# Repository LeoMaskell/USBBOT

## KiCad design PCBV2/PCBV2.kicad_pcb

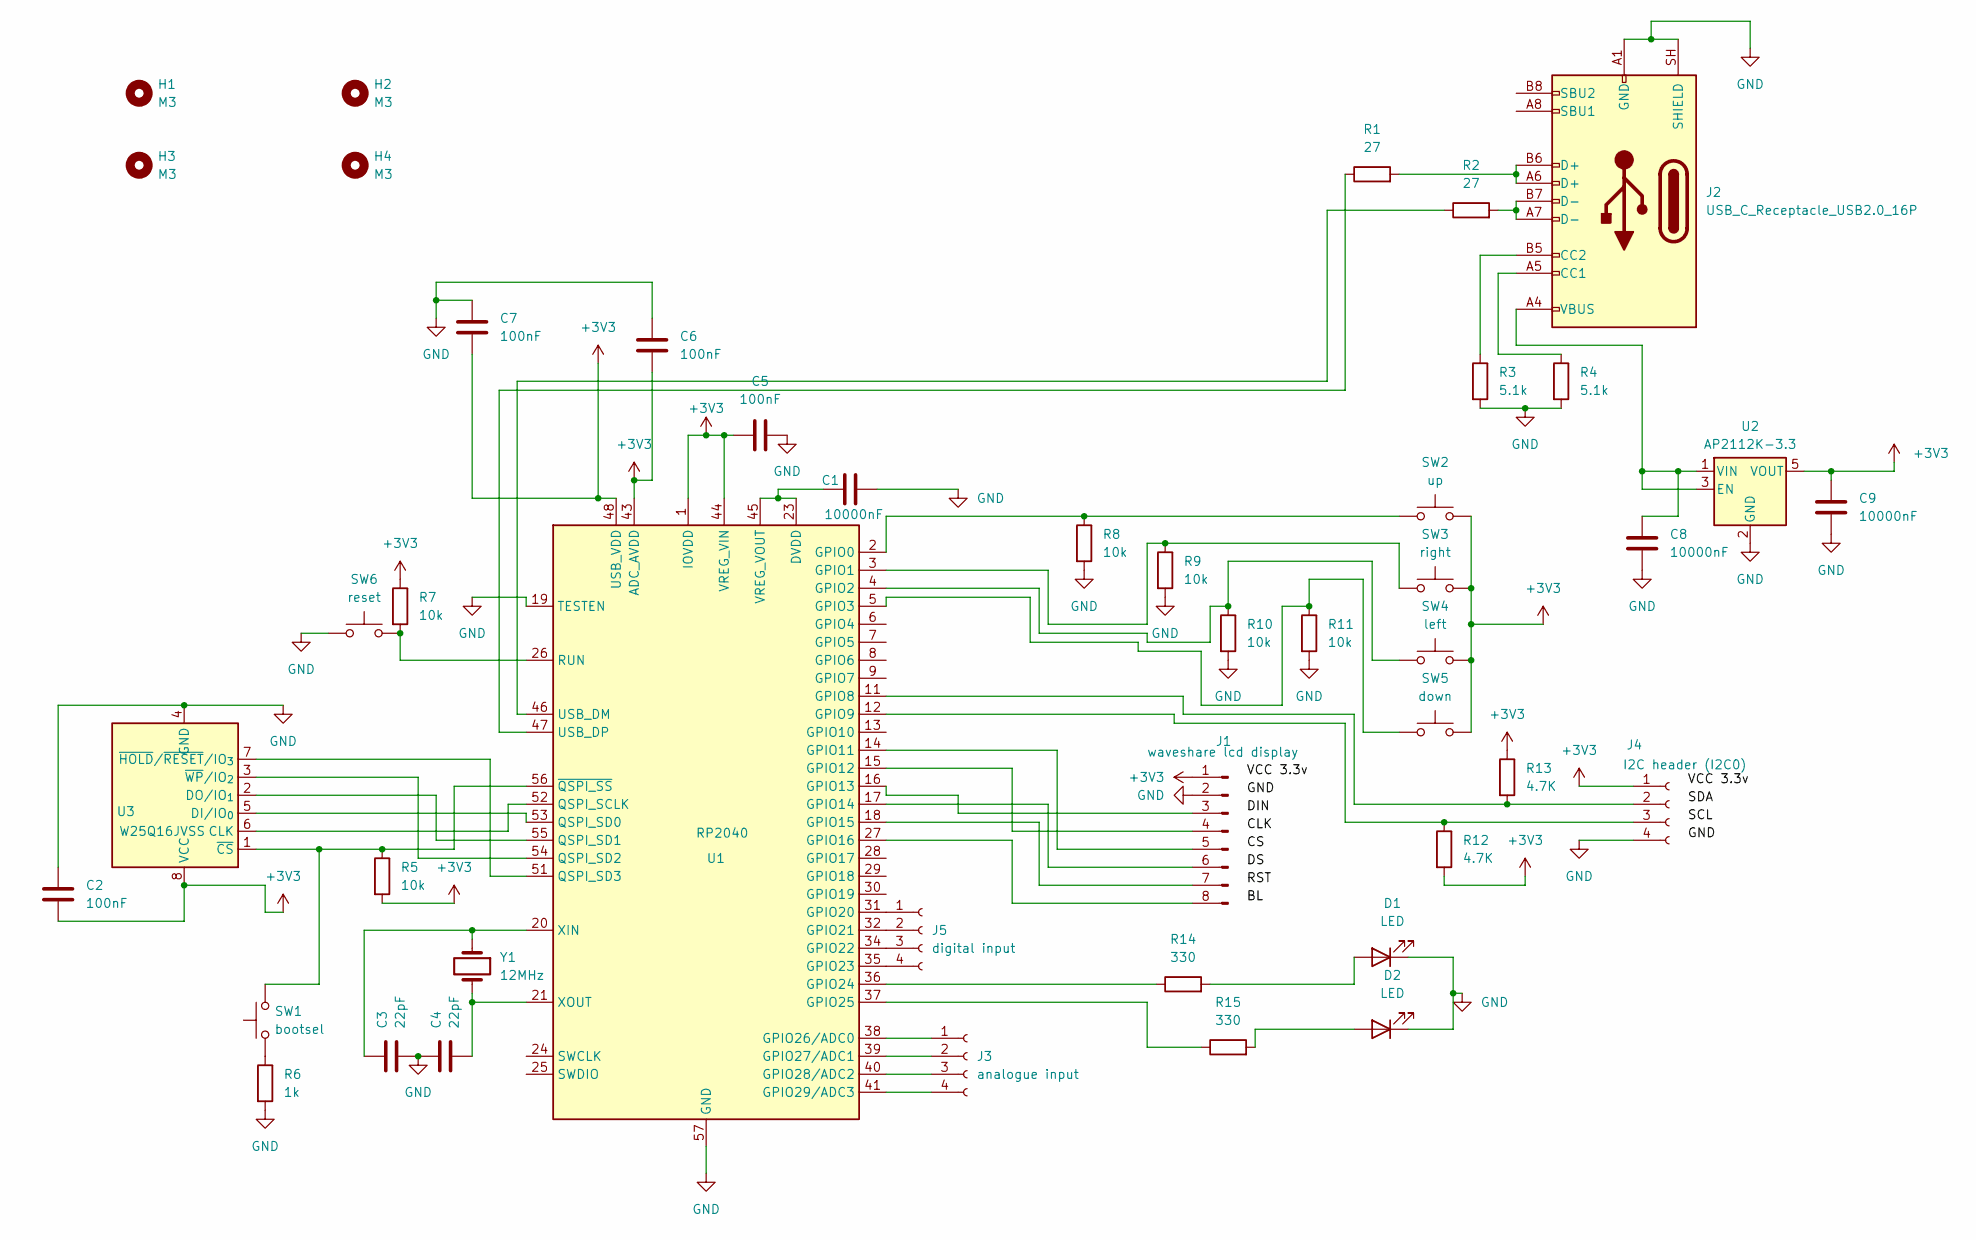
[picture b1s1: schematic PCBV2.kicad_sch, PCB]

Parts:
C1, C8, C9: 10000nF; C_0805_2012Metric
C2, C5, C6, C7: 100nF; C_0603_1608Metric
C3, C4: 22pF; C_0805_2012Metric
D1, D2: LED; LED_D4.0mm
H1, H2, H3, H4: M3; MountingHole_3.2mm_M3
J1: waveshare lcd display; PinHeader_1x08_P2.54mm_Vertical
J2: USB_C_Receptacle_USB2.0_16P; USB_C_Receptacle_Palconn_UTC16-G
J3: analogue input; PinHeader_1x04_P2.00mm_Vertical
J4: I2C header (I2C0); PinHeader_1x04_P2.00mm_Vertical
J5: digital input; PinHeader_1x04_P2.00mm_Vertical
R1, R2: 27; R_0603_1608Metric
R3, R4: 5.1k; R_0603_1608Metric
R5, R7, R8, R9, R10, R11: 10k; R_0603_1608Metric
R6: 1k; R_0603_1608Metric
R12, R13: 4.7K; R_0603_1608Metric
R14, R15: 330; R_0603_1608Metric
SW1: bootsel; SW_SPST_Omron_B3FS-100xP
SW2: up; SW_SPST_Omron_B3FS-100xP
SW3: right; SW_SPST_Omron_B3FS-100xP
SW4: left; SW_SPST_Omron_B3FS-100xP
SW5: down; SW_SPST_Omron_B3FS-100xP
SW6: reset; SW_SPST_Omron_B3FS-100xP
U1: RP2040; QFN-56-1EP_7x7mm_P0.4mm_EP3.2x3.2mm
U2: AP2112K-3.3; SOT-23-5_HandSoldering
U3: W25Q16JVSS; SOIC-8_5.3x5.3mm_P1.27mm
Y1: 12MHz; Crystal_HC49-4H_Vertical

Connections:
+3V3: C2.2, C5.1, C6.2, C7.2, C9.1, J1.1, J4.1, R5.2, R7.1, R12.2, R13.1, SW2.2, SW3.2, SW4.2, SW5.2, U1.1 (IOVDD), U1.10 (IOVDD), U1.22 (IOVDD), U1.33 (IOVDD), U1.42 (IOVDD), U1.43 (ADC_AVDD), U1.44 (VREG_VIN), U1.48 (USB_VDD), U1.49 (IOVDD), U2.5 (VOUT), U3.8 (VCC)
GND: C1.2, C2.1, C3.2, C4.1, C5.2, C6.1, C7.1, C8.2, C9.2, D1.1 (K), D2.1 (K), J1.2, J2.A1 (GND), J2.A12 (GND), J2.B1 (GND), J2.B12 (GND), J2.SH (SHIELD), J4.4, R3.2, R4.2, R6.2, R8.2, R9.2, R10.2, R11.2, SW6.1, U1.19 (TESTEN), U1.57 (GND), U2.2 (GND), U3.4 (GND)
unnamed: D1.2 (A), R14.2
unnamed: D2.2 (A), R15.2
unnamed: J1.3, U1.16 (GPIO13)
unnamed: J1.4, U1.15 (GPIO12)
unnamed: J1.5, U1.14 (GPIO11)
unnamed: J1.6, U1.17 (GPIO14)
unnamed: J1.7, U1.18 (GPIO15)
unnamed: J1.8, U1.27 (GPIO16)
unnamed: J2.A5 (CC1), R4.1
unnamed: J2.B5 (CC2), R3.1
unnamed: J2.A6 (D+), J2.B6 (D+), R1.2
unnamed: J2.A7 (D-), J2.B7 (D-), R2.2
unnamed: J3.1, U1.38 (GPIO26/ADC0)
unnamed: J3.2, U1.39 (GPIO27/ADC1)
unnamed: J3.3, U1.40 (GPIO28/ADC2)
unnamed: J3.4, U1.41 (GPIO29/ADC3)
unnamed: J4.2, R13.2, U1.11 (GPIO8)
unnamed: J4.3, R12.1, U1.12 (GPIO9)
unnamed: J5.1, U1.31 (GPIO20)
unnamed: J5.2, U1.32 (GPIO21)
unnamed: J5.3, U1.34 (GPIO22)
unnamed: J5.4, U1.35 (GPIO23)
unnamed: R6.1, SW1.1
unnamed: R8.1, SW2.1, U1.2 (GPIO0)
unnamed: R9.1, SW3.1, U1.3 (GPIO1)
unnamed: R10.1, SW4.1, U1.4 (GPIO2)
unnamed: R11.1, SW5.1, U1.5 (GPIO3)
unnamed: R14.1, U1.36 (GPIO24)
unnamed: R15.1, U1.37 (GPIO25)
unnamed: U1.52 (QSPI_SCLK), U3.6 (CLK)
unnamed: U1.53 (QSPI_SD0), U3.5 (DI/IO_{0})
unnamed: U1.55 (QSPI_SD1), U3.2 (DO/IO_{1})
unnamed: U1.54 (QSPI_SD2), U3.3 (~WP/IO_{2})
unnamed: U1.51 (QSPI_SD3), U3.7 (~HOLD/~RESET/IO_{3})
unnamed: R7.2, SW6.2, U1.26 (RUN)
unnamed: R2.1, U1.46 (USB_DM)
unnamed: R1.1, U1.47 (USB_DP)
unnamed: C1.1, U1.23 (DVDD), U1.45 (VREG_VOUT), U1.50 (DVDD)
unnamed: C3.1, U1.20 (XIN), Y1.1
unnamed: C4.2, U1.21 (XOUT), Y1.2
unnamed: R5.1, SW1.2, U1.56 (~QSPI_SS), U3.1 (~CS)
unnamed: C8.1, J2.A4 (VBUS), J2.A9 (VBUS), J2.B4 (VBUS), J2.B9 (VBUS), U2.1 (VIN), U2.3 (EN)

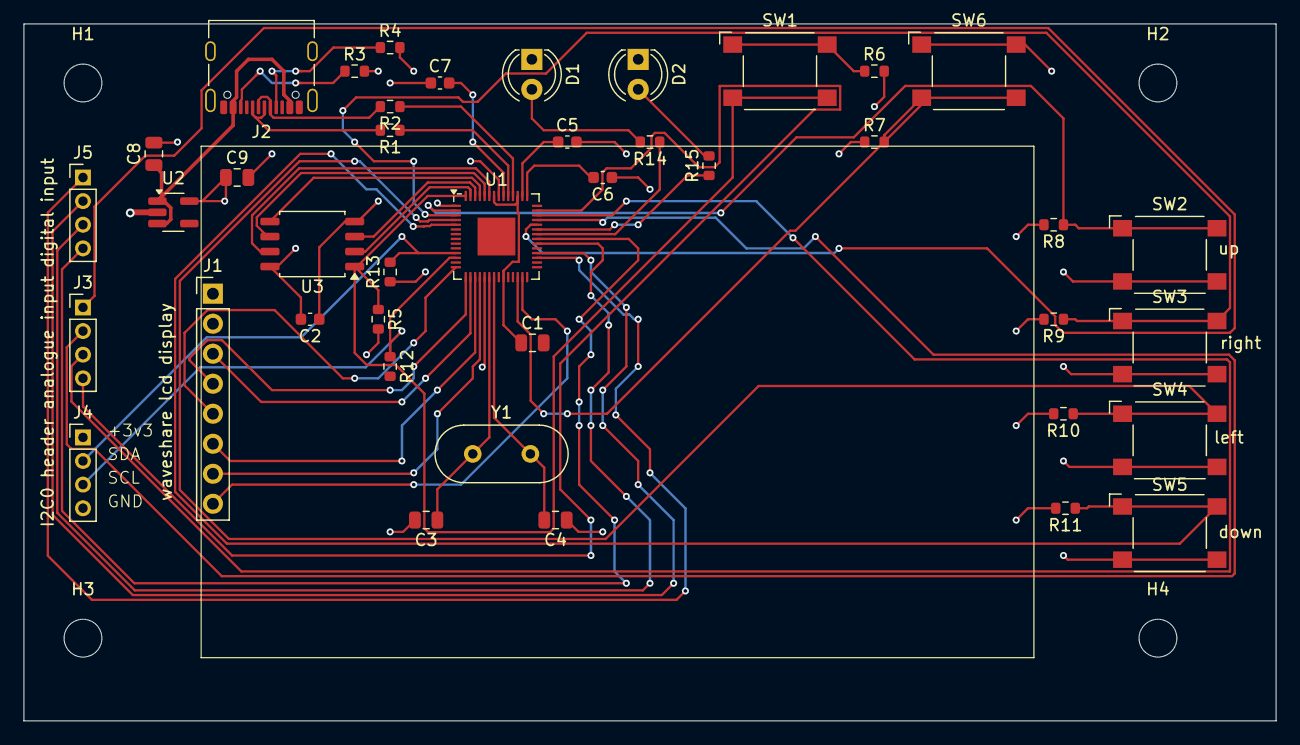
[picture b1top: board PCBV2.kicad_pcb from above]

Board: 4 copper layers, 106.0 x 59.0 mm, 45 parts (0 on the bottom side), 44 nets.
